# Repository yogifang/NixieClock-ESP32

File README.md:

# NixieClock-ESP32
Build a Clock with  Nixie Tubes 
1. MCU : ESP32-32D
2. System : Arduino 
3. Development tools : Visual Studio Code + PlatformIO + Kicad
4. Functions : Webpage Setting Wifi SSID , password & Time Zone , NTP client sync time once every day.

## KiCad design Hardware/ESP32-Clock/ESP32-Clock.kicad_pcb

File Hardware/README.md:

Download whole directory.
Open Project in Kicad (Ver 5.1.2-1).
ESP32-Clock is main board for 6 digits of Nixie Tubes.
Nixie is for IN-18.

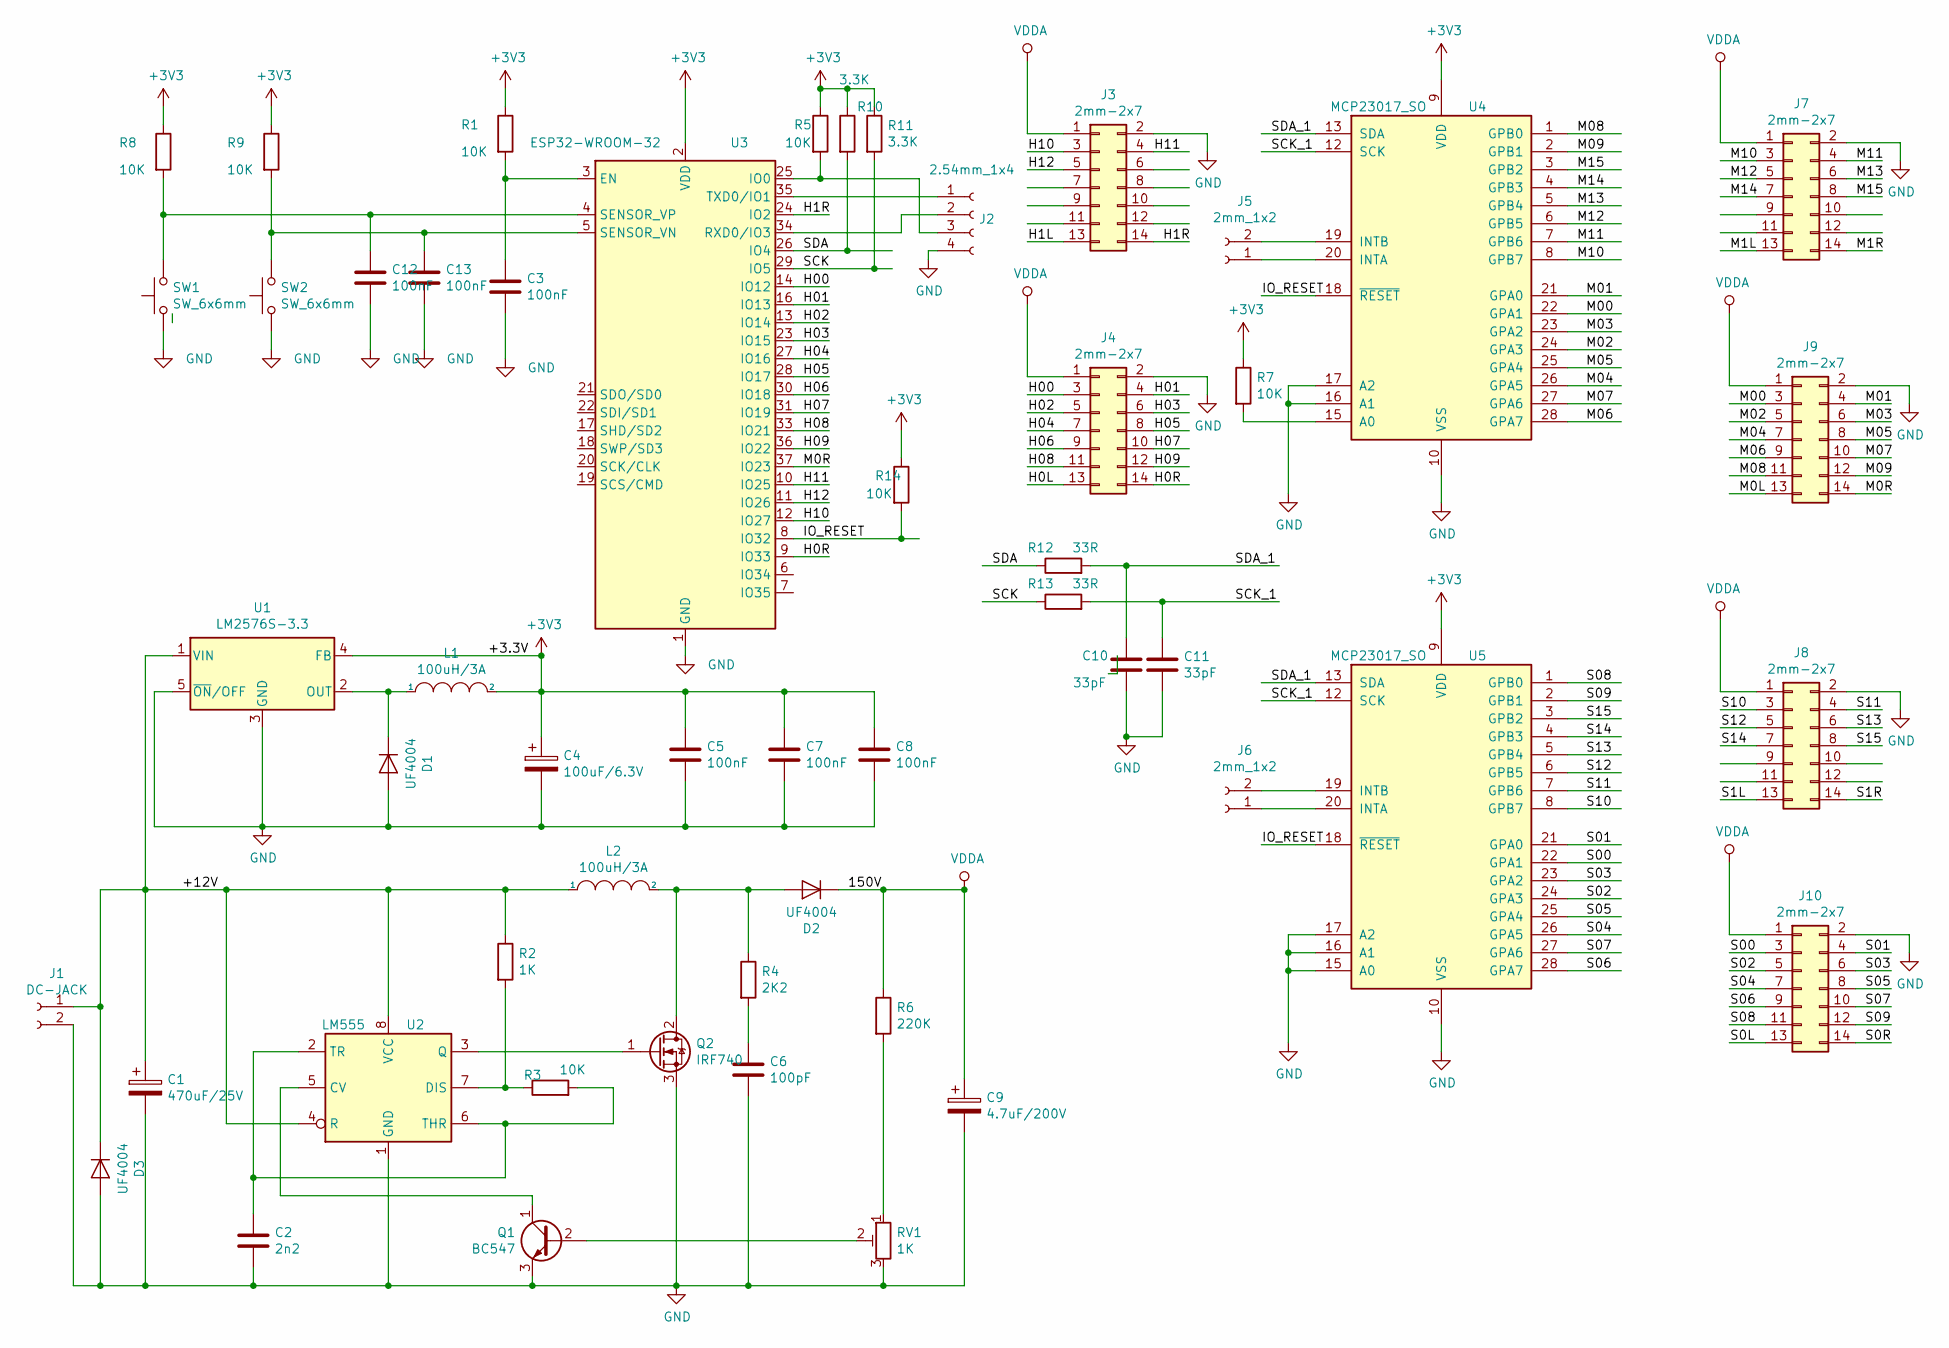
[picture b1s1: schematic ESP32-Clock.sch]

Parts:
C1: 470uF/25V; CP_Elec_10x10
C2: 2n2; C_0603_1608Metric
C3, C5, C7, C8, C12, C13: 100nF; C_0603_1608Metric
C4: 100uF/6.3V; CP_Elec_6.3x5.9
C6: 100pF; C_0603_1608Metric
C9: 4.7uF/200V; C_Radial_D8.0mm_H11.5mm_P3.50mm
C10, C11: 33pF; C_0603_1608Metric
D1, D2, D3: UF4004; D_SMA
J1: DC-JACK; BarrelJack_Horizontal
J2: 2.54mm_1x4; PinHeader_1x04_P2.54mm_Vertical
J3, J4, J7, J8, J9, J10: 2mm-2x7; PinHeader_2x07_P2.00mm_Vertical
J5, J6: 2mm_1x2; PinSocket_1x02_P2.00mm_Vertical
L1, L2: 100uH/3A; L_Toroid_Vertical_L13.0mm_W6.5mm_P5.60mm
Q1: BC547; TO-92_Inline
Q2: IRF740; TO-263-2
R1, R3, R5, R7, R8, R9, R14: 10K; R_0603_1608Metric
R2: 1K; R_0603_1608Metric
R4: 2K2; R_0805_2012Metric
R6: 220K; R_0805_2012Metric
R10, R11: 3.3K; R_0603_1608Metric
R12, R13: 33R; R_0603_1608Metric
RV1: 1K; Potentiometer_Bourns_3386P_Vertical
SW1, SW2: SW_6x6mm; SW_SPST_B3S-1000
U1: LM2576S-3.3; TO-263-5_TabPin3
U2: LM555; SOIC-8-1EP_3.9x4.9mm_P1.27mm_EP2.29x3mm_ThermalVias
U3: ESP32-WROOM-32
U4, U5: MCP23017_SO; SOIC-28W_7.5x17.9mm_P1.27mm

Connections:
+3V3: C4.1, C5.1, C7.1, C8.1, L1.2, R1.1, R5.1, R7.1, R8.1, R9.1, R10.1, R11.1, R14.1, U1.4 (FB), U3.2 (VDD), U4.9 (VDD), U5.9 (VDD)
/+12V: C1.1, D3.1 (K), J1.1, L2.1, R2.1, U1.1 (VIN), U2.4 (R), U2.8 (VCC)
/H00: J4.3, U3.14 (IO12)
/H0L: J4.13
/H0R: J4.14, U3.9 (IO33)
/H01: J4.4, U3.16 (IO13)
/H1L: J3.13
/H1R: J3.14, U3.24 (IO2)
/H02: J4.5, U3.13 (IO14)
/H03: J4.6, U3.23 (IO15)
/H04: J4.7, U3.27 (IO16)
/H05: J4.8, U3.28 (IO17)
/H06: J4.9, U3.30 (IO18)
/H07: J4.10, U3.31 (IO19)
/H08: J4.11, U3.33 (IO21)
/H09: J4.12, U3.36 (IO22)
/H10: J3.3, U3.12 (IO27)
/H11: J3.4, U3.10 (IO25)
/H12: J3.5, U3.11 (IO26)
/IO_RESET: R14.2, U3.8 (IO32), U4.18 (~RESET~), U5.18 (~RESET~)
/M00: J9.3, U4.22 (GPA1)
/M0L: J9.13
/M0R: J9.14, U3.37 (IO23)
/M01: J9.4, U4.21 (GPA0)
/M1L: J7.13
/M1R: J7.14
/M02: J9.5, U4.24 (GPA3)
/M03: J9.6, U4.23 (GPA2)
/M04: J9.7, U4.26 (GPA5)
/M05: J9.8, U4.25 (GPA4)
/M06: J9.9, U4.28 (GPA7)
/M07: J9.10, U4.27 (GPA6)
/M08: J9.11, U4.1 (GPB0)
/M09: J9.12, U4.2 (GPB1)
/M10: J7.3, U4.8 (GPB7)
/M11: J7.4, U4.7 (GPB6)
/M12: J7.5, U4.6 (GPB5)
/M13: J7.6, U4.5 (GPB4)
/M14: J7.7, U4.4 (GPB3)
/M15: J7.8, U4.3 (GPB2)
/S00: J10.3, U5.22 (GPA1)
/S0L: J10.13
/S0R: J10.14
/S01: J10.4, U5.21 (GPA0)
/S1L: J8.13
/S1R: J8.14
/S02: J10.5, U5.24 (GPA3)
/S03: J10.6, U5.23 (GPA2)
/S04: J10.7, U5.26 (GPA5)
/S05: J10.8, U5.25 (GPA4)
/S06: J10.9, U5.28 (GPA7)
/S07: J10.10, U5.27 (GPA6)
/S08: J10.11, U5.1 (GPB0)
/S09: J10.12, U5.2 (GPB1)
/S10: J8.3, U5.8 (GPB7)
/S11: J8.4, U5.7 (GPB6)
/S12: J8.5, U5.6 (GPB5)
/S13: J8.6, U5.5 (GPB4)
/S14: J8.7, U5.4 (GPB3)
/S15: J8.8, U5.3 (GPB2)
/SCK: R11.2, R13.1, U3.29 (IO5)
/SCK_1: C11.1, R13.2, U4.12 (SCK), U5.12 (SCK)
/SDA: R10.2, R12.1, U3.26 (IO4)
/SDA_1: C10.1, R12.2, U4.13 (SDA), U5.13 (SDA)
GND: C1.2, C2.2, C3.2, C4.2, C5.2, C6.2, C7.2, C8.2, C9.2, C10.2, C11.2, C12.2, C13.2, D1.2 (A), D3.2 (A), J1.2, J2.4, J3.2, J4.2, J7.2, J8.2, J9.2, J10.2, Q1.3 (E), Q2.3 (S), RV1.3, SW1.2, SW2.2, U1.3 (GND), U1.5 (~ON~/OFF), U2.1 (GND), U3.1 (GND), U3.15 (GND), U3.38 (GND), U4.10 (VSS), U4.16 (A1), U4.17 (A2), U5.10 (VSS), U5.15 (A0), U5.16 (A1), U5.17 (A2)
unnamed: C2.1, R3.2, U2.2 (TR), U2.6 (THR)
unnamed: C3.1, R1.2, U3.3 (EN)
unnamed: C6.1, R4.2
unnamed: C12.1, R8.2, SW1.1, U3.4 (SENSOR_VP)
unnamed: C13.1, R9.2, SW2.1, U3.5 (SENSOR_VN)
unnamed: D1.1 (K), L1.1, U1.2 (OUT)
unnamed: D2.2 (A), L2.2, Q2.2 (D), R4.1
unnamed: J2.1, U3.35 (TXD0/IO1)
unnamed: J2.2, U3.34 (RXD0/IO3)
unnamed: J2.3, R5.2, U3.25 (IO0)
unnamed: J5.1, U4.20 (INTA)
unnamed: J5.2, U4.19 (INTB)
unnamed: J6.1, U5.20 (INTA)
unnamed: J6.2, U5.19 (INTB)
unnamed: Q1.1 (C), U2.5 (CV)
unnamed: Q1.2 (B), RV1.2
unnamed: Q2.1 (G), U2.3 (Q)
unnamed: R2.2, R3.1, U2.7 (DIS)
unnamed: R6.2, RV1.1
unnamed: R7.2, U4.15 (A0)
VDDA: C9.1, D2.1 (K), J3.1, J4.1, J7.1, J8.1, J9.1, J10.1, R6.1

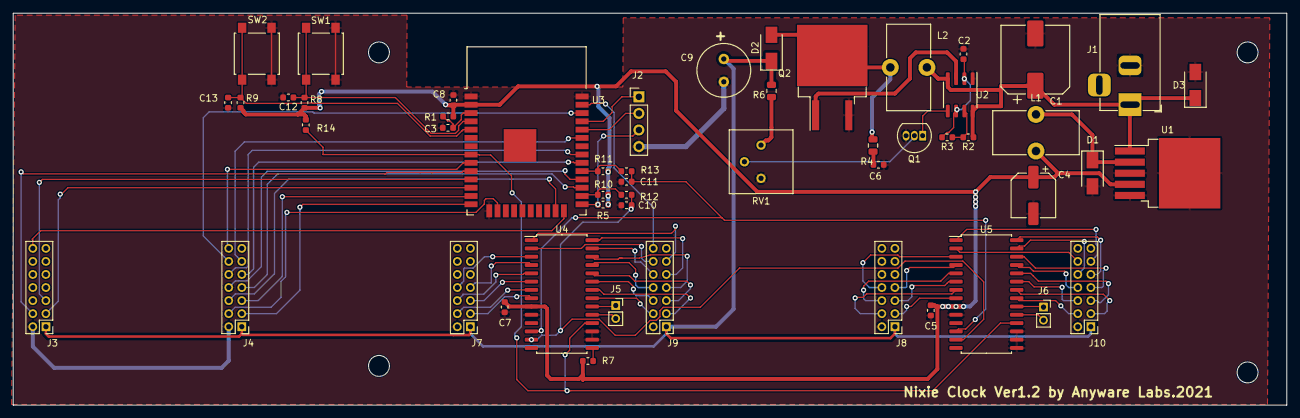
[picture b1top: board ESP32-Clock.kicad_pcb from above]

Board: 2 copper layers, 195.0 x 60.0 mm, 52 parts (0 on the bottom side), 77 nets.

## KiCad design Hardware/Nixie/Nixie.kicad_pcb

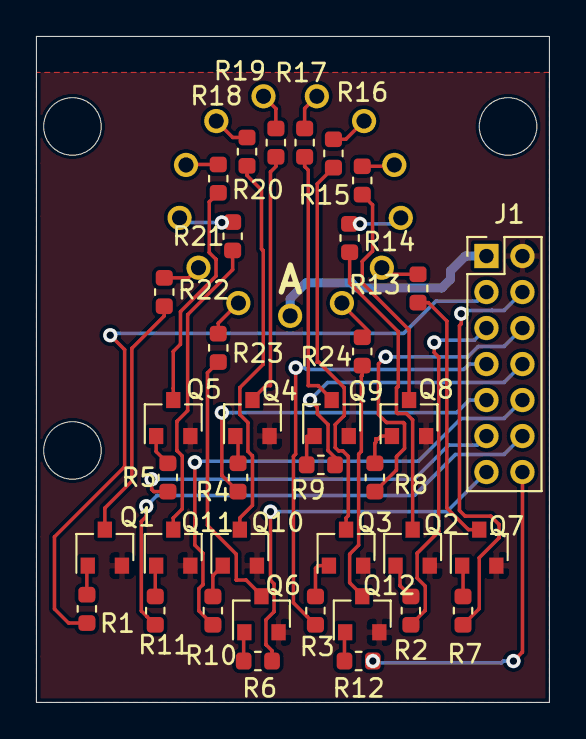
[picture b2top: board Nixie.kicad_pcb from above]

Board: 2 copper layers, 28.5 x 37.0 mm, 38 parts (1 on the bottom side), 50 nets.

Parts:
J1: 2x7_2.54mm; PinHeader_2x07_P2.00mm_Vertical
N1: IN-14; nixies-us-IN-14
Q1, Q2, Q3, Q4, Q5, Q6, Q7, Q8, Q9, Q10, Q11, Q12: BSS139; SOT-23
R1, R2, R3, R4, R5, R6, R7, R8, R9, R10, R11, R12, R13, R14, R15, R16, R17, R18, R19, R20, R21, R22, R23, R24: 10K; R_0603_1608Metric

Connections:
/+150V: J1.1, N1.A
/O0: Q1.3, R22.1
/O1: Q7.3, R13.1
/O2: Q2.3, R14.1
/O3: Q8.3, R15.1
/O4: Q3.3, R16.1
/O5: Q9.3, R17.1
/O6: Q4.3, R18.1
/O7: Q10.3, R19.1
/O8: Q5.3, R20.1
/O9: Q11.3, R21.1
/OLD: Q6.3, R23.2
/ORD: Q12.3, R24.2
/P0: J1.3, R1.1
/P1: J1.4, R7.1
/P2: J1.5, R2.1
/P3: J1.6, R8.1
/P4: J1.7, R3.1
/P5: J1.8, R9.1
/P6: J1.9, R4.1
/P7: J1.10, R10.1
/P8: J1.11, R5.1
/P9: J1.12, R11.1
/PLD: J1.13, R6.1
/PRD: J1.14, R12.1
GND: J1.2, Q1.2, Q2.2, Q3.2, Q4.2, Q5.2, Q6.2, Q7.2, Q8.2, Q9.2, Q10.2, Q11.2, Q12.2
unnamed: N1.0, R22.2
unnamed: N1.1, R13.2
unnamed: N1.2, R14.2
unnamed: N1.3, R15.2
unnamed: N1.4, R16.2
unnamed: N1.5, R17.2
unnamed: N1.6, R18.2
unnamed: N1.7, R19.2
unnamed: N1.8, R20.2
unnamed: N1.9, R21.2
unnamed: N1.LHDP, R23.1
unnamed: N1.RHDP, R24.1
unnamed: Q1.1, R1.2
unnamed: Q2.1, R2.2
unnamed: Q3.1, R3.2
unnamed: Q4.1, R4.2
unnamed: Q5.1, R5.2
unnamed: Q6.1, R6.2
unnamed: Q7.1, R7.2
unnamed: Q8.1, R8.2
unnamed: Q9.1, R9.2
unnamed: Q10.1, R10.2
unnamed: Q11.1, R11.2
unnamed: Q12.1, R12.2

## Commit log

2021-05-04 Project Create
2021-05-04 Enlarge Font size Of Setting Page
2021-05-04 error steps
2021-05-07 Add Push SW1 to portal function
2021-06-04 bug fixed 2021-0604
2021-06-04 remove ingored files
2021-06-06 add image to readme.md
2022-01-08 update 0108
2022-01-16 Library updated
